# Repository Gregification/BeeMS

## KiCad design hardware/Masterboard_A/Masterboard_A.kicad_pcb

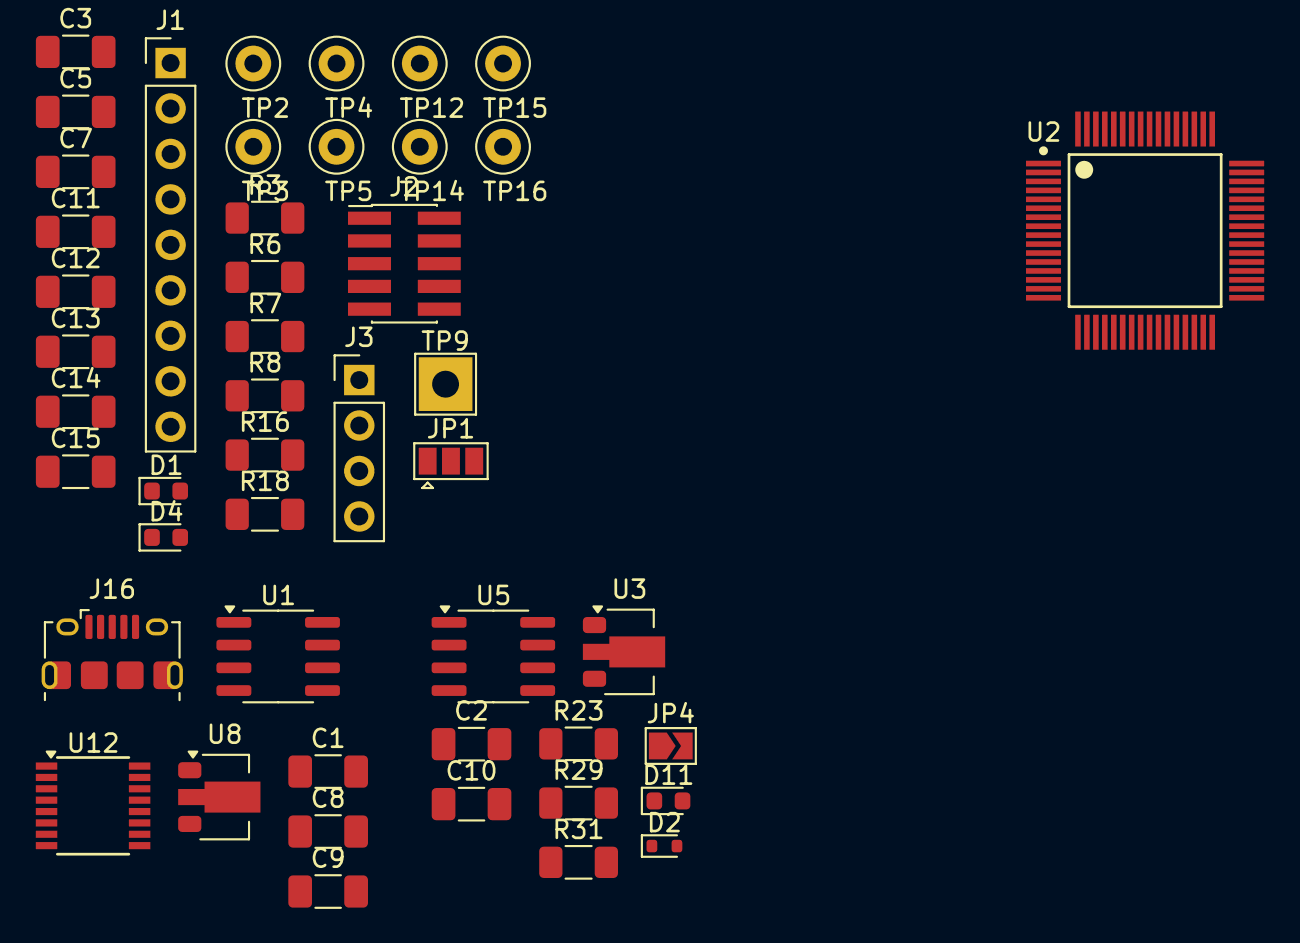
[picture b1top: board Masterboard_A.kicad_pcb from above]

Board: 2 copper layers, 47 parts (0 on the bottom side), 33 nets, no tracks yet.

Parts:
C1, C2, C8, C10, C14: 10u; C_1206_3216Metric_Pad1.33x1.80mm_HandSolder
C3, C15: 100n; C_1206_3216Metric_Pad1.33x1.80mm_HandSolder
C5, C7, C9, C11, C12, C13: 220n; C_1206_3216Metric_Pad1.33x1.80mm_HandSolder
D1, D4, D11: LED; LED_0603_1608Metric
D2: 1N4148WT; D_SOD-523
J1: Conn_01x09_Socket; PinHeader_1x09_P2.54mm_Vertical
J2: Conn_02x05_Odd_Even; PinHeader_2x05_P1.27mm_Vertical_SMD
J3: Conn_01x04_Pin; PinHeader_1x04_P2.54mm_Vertical
J16: USB_B_Micro; USB_Micro-B_Amphenol_10118194-0001LF_Horizontal
JP1: SolderJumper_3_Open; SolderJumper-3_P1.3mm_Open_Pad1.0x1.5mm
JP4: SolderJumper_2_Open; SolderJumper-2_P1.3mm_Open_TrianglePad1.0x1.5mm
R3, R6, R31: 750; R_1206_3216Metric_Pad1.30x1.75mm_HandSolder
R7, R23: 49.9k; R_1206_3216Metric_Pad1.30x1.75mm_HandSolder
R8: 100k; R_1206_3216Metric_Pad1.30x1.75mm_HandSolder
R16, R18, R29: 4.99k; R_1206_3216Metric_Pad1.30x1.75mm_HandSolder
TP2, TP3, TP4, TP5, TP12, TP14, TP15, TP16: TestPoint; TestPoint_Loop_D2.50mm_Drill1.0mm_LowProfile
TP9: TestPoint; TestPoint_THTPad_3.0x3.0mm_Drill1.5mm
U1, U5: ISO7721D; SOIC-8_3.9x4.9mm_P1.27mm
U2: MCU-MSM0G3507SPM; MSPM0G3507-64-IPC_A
U3, U8: L78L05_SOT89; SOT-89-3
U12: FT230XS; SSOP-16_3.9x4.9mm_P0.635mm

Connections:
/GLV CAN TRX/5v: JP4.2 (B), U5.1 (VCC1)
/GLV CAN TRX/-GLV: C2.2, C10.2, D11.1 (K), J3.3, R23.1, R29.2, U3.2 (GND), U5.4 (GND1)
/GLV CAN TRX/CAN_VDD: D2.2 (A), J3.4
/XDS_3v_supply: J1.3, J2.1, JP1.1 (A), TP5.1
GND: C3.2, C5.2, C7.2, C11.2, C12.2, C13.2, C14.2, C15.2, D1.1 (K), D4.1 (K), J1.1, J2.3, J2.5, J2.7, J2.9, R8.1, TP9.1, TP14.1, TP15.1, TP16.1, U1.5 (GND2), U2.41 (VSS), U5.5 (GND2)
unnamed: D1.2 (A), R6.1
unnamed: C10.1, D2.1 (K), U3.3 (IN)
unnamed: D4.2 (A), R3.2
unnamed: D11.2 (A), R31.2
unnamed: J16.3 (D+), U12.8 (USBDP)
unnamed: J16.2 (D-), U12.9 (USBDM)
unnamed: C1.2, C8.2, C9.2, J16.5 (GND), U1.4 (GND1), U8.2 (GND), U12.5 (GND), U12.13 (GND)
unnamed: C1.1, J16.1 (VBUS), U8.3 (IN)
unnamed: C2.1, JP4.1 (A), R31.1, U3.1 (OUT)
unnamed: U1.3 (INB), U12.1 (TXD)
unnamed: U1.2 (OUTA), U12.4 (RXD)
unnamed: C8.1, C9.1, U1.1 (VCC1), U8.1 (OUT), U12.3 (VCCIO), U12.12 (VCC)
unnamed: R8.2, U2.42 (PA2_ROSC)
unnamed: TP2.1, U2.64 (PB12)
unnamed: C5.1, C11.1, TP3.1, U2.32 (VCORE)
unnamed: R29.1, U5.2 (OUTA)
PA10_UART0-TX_XDS: J1.5, U1.7 (INA), U2.56 (PA10)
PA11_UART0-RX_XDS: J1.4, U1.6 (OUTB), U2.57 (PA11)
PA12_CAN_TX: U2.5 (PA12_CAN_TX), U5.7 (INA)
PA13_CAN_RX: U2.6 (PA13_CAN_RX), U5.6 (OUTB)
PA14: R3.1, U2.7 (PA14)
PA15_I2C1_SCL: R16.1, U2.8 (PA15_A1_0)
PA16_I2C1_SDA: R18.2, U2.9 (PA16_A1_1)
PA19_SWDIO: J1.7, J2.2, U2.12 (PA19_SWDIO)
PA20_SWCLK: J1.8, J2.4, U2.13 (PA20_SWCLK)
RST_N: C3.1, J1.6, J2.10, R7.2, U2.38 (RST_N)
VDD: C7.1, C12.1, C13.1, C14.1, C15.1, JP1.2 (C), R6.2, R7.1, R16.2, R18.1, TP4.1, U1.8 (VCC2), U2.40 (VDD), U5.8 (VCC2)
onboard 3.3v src: JP1.3 (B), TP12.1

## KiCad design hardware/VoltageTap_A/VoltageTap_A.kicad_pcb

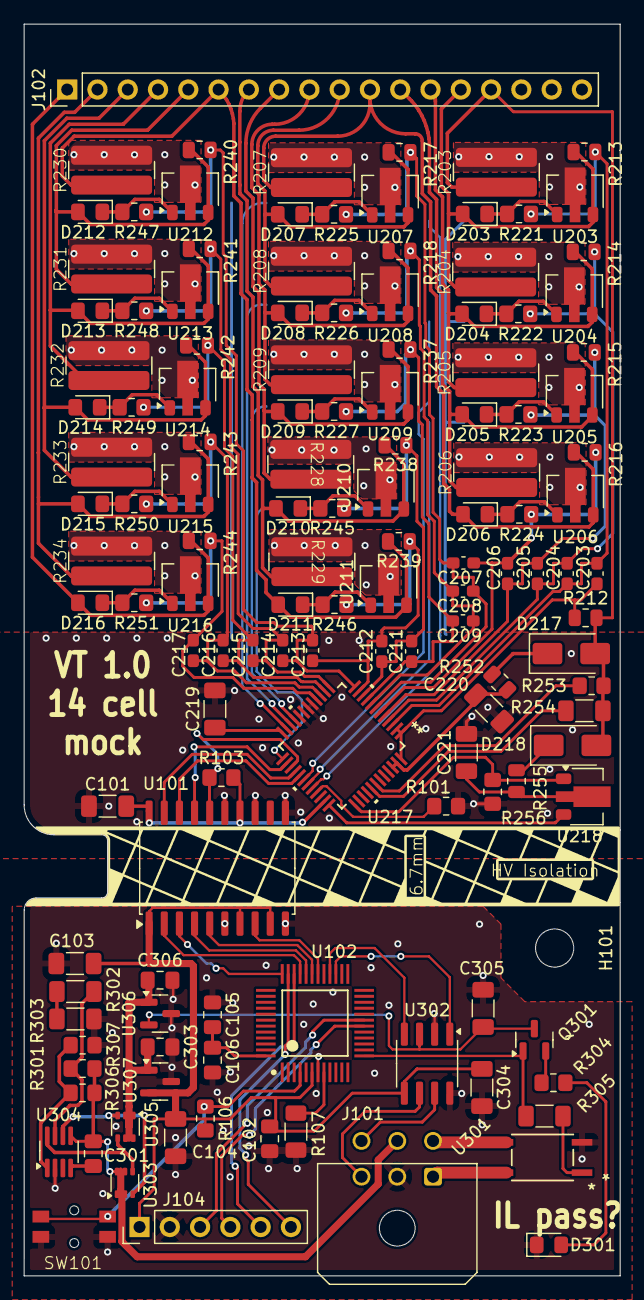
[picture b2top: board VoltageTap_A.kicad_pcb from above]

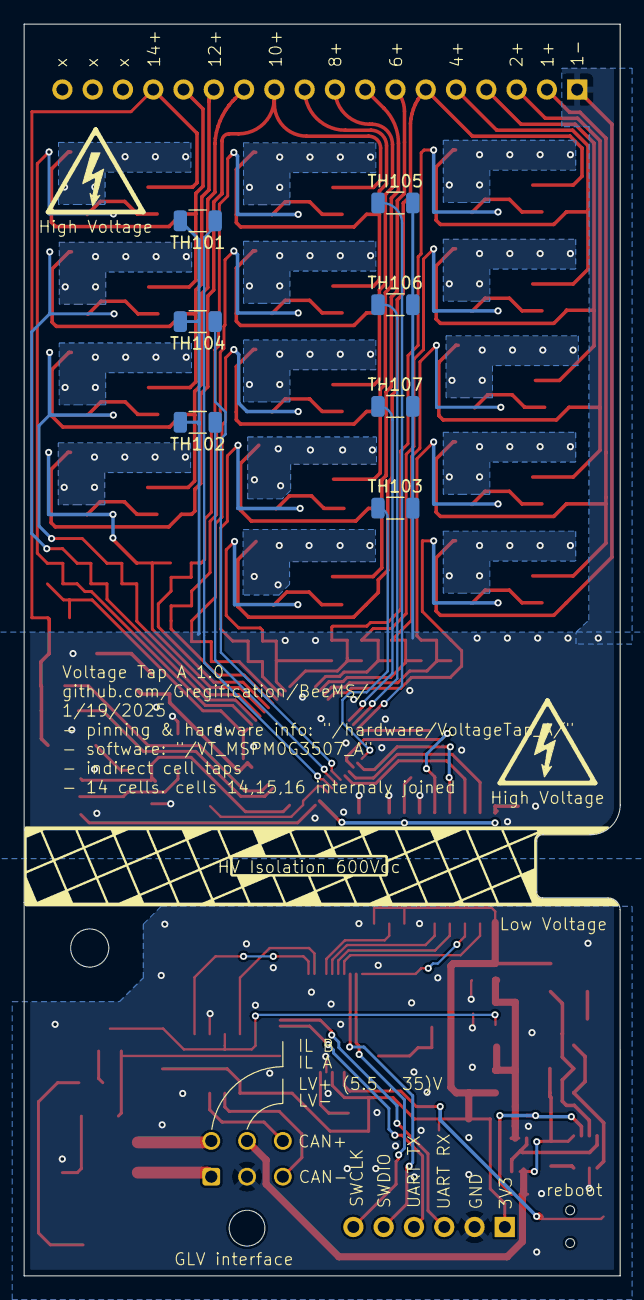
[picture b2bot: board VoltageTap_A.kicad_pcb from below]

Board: 2 copper layers, 50.0 x 105.0 mm, 142 parts (7 on the bottom side), 113 nets.

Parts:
C101, C103, C220, C221: 1u; C_1206_3216Metric_Pad1.33x1.80mm_HandSolder
C102, C105, C106, C301, C303, C306: 220n; C_0805_2012Metric_Pad1.18x1.45mm_HandSolder
C104, C219, C304, C305: 10u; C_1206_3216Metric_Pad1.33x1.80mm_HandSolder
C203, C204, C205, C206, C207, C208, C209, C211, C212, C213, C214, C215, C216, C217: 100n; C_0603_1608Metric_Pad1.08x0.95mm_HandSolder
D203, D204, D205, D206, D207, D208, D209, D210, D211, D212, D213, D214, D215, D216: TS4148; D_0805_2012Metric_Pad1.15x1.40mm_HandSolder
D217, D218: ES1D; D_SMA
D301: green; LED_0805_2012Metric_Pad1.15x1.40mm_HandSolder
H101: MountingHole; MountingHole_3.2mm_M3
J101: HRLV; Molex_Micro-Fit_3.0_43045-0600_2x03_P3.00mm_Horizontal
J102: Conn_01x18_Pin; PinHeader_1x18_P2.54mm_Vertical
J104: Conn_01x06_Pin; PinHeader_1x06_P2.54mm_Vertical
Q301: MMBT5550L; SOT-23
R101: 88.7k; R_0805_2012Metric_Pad1.20x1.40mm_HandSolder
R103, R253, R256, R307: 10k; R_0805_2012Metric_Pad1.20x1.40mm_HandSolder
R106: 40.2k; R_0805_2012Metric_Pad1.20x1.40mm_HandSolder
R107: 100k; R_1206_3216Metric_Pad1.30x1.75mm_HandSolder
R203, R204, R205, R206, R207, R208, R209, R228, R229, R230, R231, R232, R233, R234: 36; imperial wide resistor R_ 3264
R212, R213, R214, R215, R216, R217, R218, R237, R238, R239, R240, R241, R242, R243, R244, R252, R255: 100; R_0805_2012Metric
R221, R222, R223, R224, R225, R226, R227, R245, R246, R247, R248, R249, R250, R251: 226; R_0805_2012Metric_Pad1.20x1.40mm_HandSolder
R254, R302: 4.99k; R_1206_3216Metric_Pad1.30x1.75mm_HandSolder
R301, R306: 97.6k; R_0805_2012Metric_Pad1.20x1.40mm_HandSolder
R303, R305: 750; R_1206_3216Metric_Pad1.30x1.75mm_HandSolder
R304: 2.4k; R_0805_2012Metric_Pad1.20x1.40mm_HandSolder
SW101: SW_Push; wurth elektronik 4.7x3.5mm side push button
TH101, TH102, TH103, TH104, TH105, TH106, TH107: Thermistor; R_1206_3216Metric
U101: ISOW7741; SOIC-20W_7.5x12.8mm_P1.27mm
U102: XM0G3507QPTRQ1; PT0048A-IPC_B
U203, U204, U205, U206, U207, U208, U209, U210, U211, U212, U213, U214, U215, U216: 2PD2150-QX; SOT-89-3
U217: PBQ76952PFBT; BQ76952_PFB48_TEX
U218: FCX495; SOT-89-3
U301: ISOM8600DFGR; SOIC4_DFG_TEX-M
U302: MCP2542FDxMF; SOIC-8_3.9x4.9mm_P1.27mm
U303, U305: Si1450DH; SOT-363_SC-70-6
U304: LM74502; SOT-23-8_Handsoldering
U306: AP7384-50SA; SOT-23
U307: AP7381-33SA-7; SOT-23

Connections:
+3V3: C102.1, C103.1, C104.1, C304.1, J104.1, R106.2, U101.1 (V_{IO}), U101.7 (EN_IO1), U101.9 (V_{DD}), U102.6 (VDD), U302.5 (VIO), U307.2 (VO)
+BATT: D217.2 (A), D218.2 (A), J102.15, R203.2, R212.2, R253.2, R254.1
-BATT: C101.1, C219.2, C220.2, C221.2, D216.2 (A), J102.1, R101.1, R244.2, R256.1, TH101.2, TH102.2, TH103.2, TH104.2, TH105.2, TH106.2, TH107.2, U101.11 (GND2), U101.13 (VSEL), U101.15 (GISOIN), U216.3 (E), U217.17 (VSS), U217.18 (SRP), U217.20 (SRN)
/BQ0_3.3v: C101.2, R103.2, U101.14 (EN_IO2), U101.20 (V_{ISOIN}), U217.35 (REG1)
/BQ76952 16C/1P: D215.2 (A), J102.2, R234.2, R243.2, U215.3 (E)
/BQ76952 16C/2P: D214.2 (A), J102.3, R233.2, R242.2, U214.3 (E)
/BQ76952 16C/3P: D213.2 (A), J102.4, R232.2, R241.2, U213.3 (E)
/BQ76952 16C/4P: D212.2 (A), J102.5, R231.2, R240.2, U212.3 (E)
/BQ76952 16C/5P: D211.2 (A), J102.6, R230.2, R239.2, U211.3 (E)
/BQ76952 16C/6P: D210.2 (A), J102.7, R229.2, R238.2, U210.3 (E)
/BQ76952 16C/7P: D209.2 (A), J102.8, R228.2, R237.2, U209.3 (E)
/BQ76952 16C/8P: D208.2 (A), J102.9, R209.2, R218.2, U208.3 (E)
/BQ76952 16C/9P: D207.2 (A), J102.10, R208.2, R217.2, U207.3 (E)
/BQ76952 16C/10P: D206.2 (A), J102.11, R207.2, R216.2, U206.3 (E)
/BQ76952 16C/11P: D205.2 (A), J102.12, R206.2, R215.2, U205.3 (E)
/BQ76952 16C/12P: D204.2 (A), J102.13, R205.2, R214.2, U204.3 (E)
/BQ76952 16C/13P: D203.2 (A), J102.14, R204.2, R213.2, U203.3 (E)
/BQ76952 16C/ALERT: TH103.1, U217.25 (ALERT)
/BQ76952 16C/BAT: C220.1, R252.1, U217.46 (CP1), U217.47 (BAT)
/BQ76952 16C/C1Jc: R234.1, U216.2 (C)
/BQ76952 16C/C2Jc: R233.1, U215.2 (C)
/BQ76952 16C/C3Jc: R232.1, U214.2 (C)
/BQ76952 16C/C4Jc: R231.1, U213.2 (C)
/BQ76952 16C/C5Jc: R230.1, U212.2 (C)
/BQ76952 16C/C6Jc: R229.1, U211.2 (C)
/BQ76952 16C/C7Jc: R228.1, U210.2 (C)
/BQ76952 16C/C8Jc: R209.1, U209.2 (C)
/BQ76952 16C/C9Jc: R208.1, U208.2 (C)
/BQ76952 16C/C10Jc: R207.1, U207.2 (C)
/BQ76952 16C/C11Jc: R206.1, U206.2 (C)
/BQ76952 16C/C12Jc: R205.1, U205.2 (C)
/BQ76952 16C/C13Jc: R204.1, U204.2 (C)
/BQ76952 16C/C14Jc: R203.1, U203.2 (C)
/BQ76952 16C/CFETOFF: U101.18 (OUTB), U217.29 (CFETOFF)
/BQ76952 16C/DCHG: TH102.1, U217.31 (DCHG)
/BQ76952 16C/DDSG: TH101.1, U217.32 (DDSG)
/BQ76952 16C/DFETOFF: TH104.1, U217.30 (DFETOFF)
/BQ76952 16C/HDQ: U101.19 (OUTA), U217.28 (HDQ)
/BQ76952 16C/RST_SHUT: R101.2, U217.33 (RST_SHUT)
/BQ76952 16C/SCL: U101.17 (OUTC), U217.26 (SCL)
/BQ76952 16C/SDA: R103.1, U101.16 (IND), U217.27 (SDA)
/BQ76952 16C/TS1: TH107.1, U217.21 (TS1)
/BQ76952 16C/TS2: TH106.1, U217.22 (TS2)
/BQ76952 16C/TS3: TH105.1, U217.23 (TS3)
/CAN+: J101.6, U302.7 (CANH)
/CAN-: J101.3, U302.6 (CANL)
/GLV+: C301.1, J101.5, R301.2, R306.2, U303.1 (D), U303.2 (D), U303.5 (D), U303.6 (D), U304.5 (VS)
/HRLV interface/+5V: C305.1, Q301.3 (C), U302.3 (VDD), U306.2 (VO)
/HRLV interface/CAN_RX: U102.28 (PA13), U302.4 (RXD)
/HRLV interface/CAN_TX: U102.27 (PA12_FCC_IN), U302.1 (TXD)
/HRLV interface/IL enable: Q301.1 (B), R305.2, U102.13 (PA7_CLK_OUT)
/HRLV interface/LV+: C303.1, C306.1, U305.1 (D), U305.2 (D), U305.5 (D), U305.6 (D), U306.1 (VI), U307.1 (VI)
/HRLV interface/passing: U303.4 (S), U304.8 (SRC), U305.4 (S)
/IL+: J101.1, U301.4
/IL-: J101.4, U301.3
GND: C102.2, C103.2, C104.2, C105.2, C106.2, C303.2, C304.2, C305.2, C306.2, D301.1 (K), J101.2, J104.2, R107.1, R303.1, R307.1, SW101.2, U101.6 (GNDIO), U101.10 (GND1), U102.7 (VSS), U301.2, U302.2 (VSS), U302.8 (STBY), U304.2 (GND), U306.3 (GND), U307.3 (GND)
unnamed: C221.1, R255.1, U218.2
unnamed: D203.1 (K), R221.2, U203.1 (B)
unnamed: D204.1 (K), R222.2, U204.1 (B)
unnamed: D205.1 (K), R223.2, U205.1 (B)
unnamed: D206.1 (K), R224.2, U206.1 (B)
unnamed: D207.1 (K), R225.2, U207.1 (B)
unnamed: D208.1 (K), R226.2, U208.1 (B)
unnamed: D209.1 (K), R227.2, U209.1 (B)
unnamed: D210.1 (K), R245.2, U210.1 (B)
unnamed: D211.1 (K), R246.2, U211.1 (B)
unnamed: D212.1 (K), R247.2, U212.1 (B)
unnamed: D213.1 (K), R248.2, U213.1 (B)
unnamed: D214.1 (K), R249.2, U214.1 (B)
unnamed: D215.1 (K), R250.2, U215.1 (B)
unnamed: D216.1 (K), R251.2, U216.1 (B)
unnamed: D217.1 (K), R252.2
unnamed: D218.1 (K), R255.2
unnamed: D301.2 (A), R304.1
unnamed: Q301.2 (E), R304.2
unnamed: R302.1, R303.2
unnamed: R305.1, U301.1
unnamed: R107.2, U102.8 (PA2_ROSC)
unnamed: C105.1, C106.1, U102.48 (VCORE)
unnamed: R256.2, U217.37 (BREG), U218.1
unnamed: R254.2, U217.41 (LD)
unnamed: R253.1, U217.42 (PACK)
unnamed: C219.1, U217.24 (REG18)
unnamed: U217.36 (REGIN), U218.3
unnamed: C217.2, R244.1, R251.1, U217.16 (VC0)
unnamed: C216.2, C217.1, R243.1, R250.1, U217.15 (VC1)
unnamed: C215.2, C216.1, R242.1, R249.1, U217.14 (VC2)
unnamed: C214.2, C215.1, R241.1, R248.1, U217.13 (VC3)
unnamed: C213.2, C214.1, R240.1, R247.1, U217.12 (VC4)
unnamed: C212.2, C213.1, R239.1, R246.1, U217.11 (VC5)
unnamed: C211.2, C212.1, R238.1, R245.1, U217.10 (VC6)
unnamed: C209.2, C211.1, R227.1, R237.1, U217.9 (VC7)
unnamed: C208.2, C209.1, R218.1, R226.1, U217.8 (VC8)
unnamed: C207.2, C208.1, R217.1, R225.1, U217.7 (VC9)
unnamed: C206.2, C207.1, R216.1, R224.1, U217.6 (VC10)
unnamed: C205.2, C206.1, R215.1, R223.1, U217.5 (VC11)
unnamed: C204.2, C205.1, R214.1, R222.1, U217.4 (VC12)
unnamed: C203.2, C204.1, R213.1, R221.1, U217.3 (VC13)
unnamed: C203.1, R212.1, U217.1 (VC15), U217.2 (VC14), U217.48 (VC16)
unnamed: U303.3 (G), U304.6 (GATE), U305.3 (G)
unnamed: R306.1, R307.2, U304.1 (EN/UVLO)
unnamed: R301.1, R302.2, U304.7 (OV)
unnamed: C301.2, U304.4 (VCAP)
PA10_UART0-TX_XDS: J104.4, U102.18 (PA10_CLK_OUT)
PA11_UART0-RX_XDS: J104.3, U102.19 (PA11)
PA16_SPI1_MISO: U101.5 (OUTD), U102.31 (PA16_A1_1_FCC_IN)
PA17_SPI1_SCK: U101.4 (INC), U102.32 (PA17_A1_2)
PA18_SPI1_MOSI: U101.2 (INA), U102.33 (PA18_A1_3)
PA19_SWDIO: J104.5, U102.34 (PA19_SWDIO)
PA20_SWCLK: J104.6, U102.35 (PA20_SWCLK)
PA20_SWCLK_EN/FLT: U101.8 (EN/FLT), U102.30 (PA15_A1_0)
PB17_BBQ_CS: U101.3 (INB), U102.36 (PB17_A1_4)
RST_N: R106.1, SW101.1, U102.4 (RST_N)

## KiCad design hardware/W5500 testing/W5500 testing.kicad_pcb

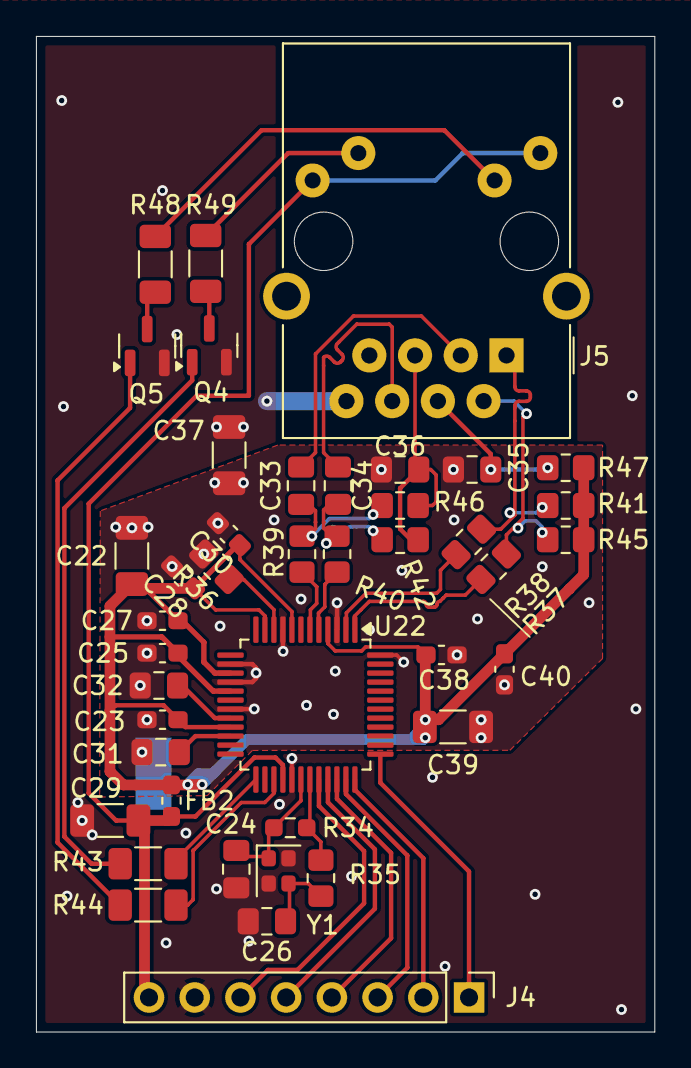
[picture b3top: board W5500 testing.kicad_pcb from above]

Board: 2 copper layers, 34.4 x 55.3 mm, 43 parts (1 on the bottom side), 36 nets.

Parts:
C22, C29, C39: 10u; C_1206_3216Metric_Pad1.33x1.80mm_HandSolder
C23, C25, C27, C28, C30, C38, C40: 100n; C_0603_1608Metric_Pad1.08x0.95mm_HandSolder
C24, C26: 18p; C_0805_2012Metric_Pad1.18x1.45mm_HandSolder
C31, C36: 10n; C_0805_2012Metric_Pad1.18x1.45mm_HandSolder
C32: 4.7u; C_0805_2012Metric_Pad1.18x1.45mm_HandSolder
C33, C34: 6.8n; C_0805_2012Metric_Pad1.18x1.45mm_HandSolder
C35: 22n; C_0805_2012Metric_Pad1.18x1.45mm_HandSolder
C37: 1n 2kV; C_1206_3216Metric_Pad1.33x1.80mm_HandSolder
FB2: L_0603_1608Metric_Pad1.05x0.95mm_HandSolder
J4: Conn_01x08_Pin; PinHeader_1x08_P2.54mm_Vertical
J5: RJ45_Amphenol_RJMG1BD3B8K1ANR
NT1: NetTie_2; NetTie-2_SMD_Pad2.0mm
Q4, Q5: MMBT5550L; SOT-23
R34: 1M; R_0603_1608Metric_Pad0.98x0.95mm_HandSolder
R35: 0; R_0805_2012Metric_Pad1.20x1.40mm_HandSolder
R36: 12.4k; R_0805_2012Metric_Pad1.20x1.40mm_HandSolder
R37, R38, R39, R40: 14.3; R_0805_2012Metric_Pad1.20x1.40mm_HandSolder
R41, R42, R45, R46: 49.9; R_0805_2012Metric_Pad1.20x1.40mm_HandSolder
R43, R44: 4.99k; R_1206_3216Metric_Pad1.30x1.75mm_HandSolder
R47: 10; R_0805_2012Metric_Pad1.20x1.40mm_HandSolder
R48, R49: 332; R_1206_3216Metric_Pad1.30x1.75mm_HandSolder
U22: W5500; LQFP-48_7x7mm_P0.5mm
Y1: Crystal_GND24; Crystal_SMD_2016-4Pin_2.0x1.6mm

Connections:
/3v3: C29.1, FB2.1, J4.8, J5.L1, J5.L4, U22.28 (VDD)
/GND: C24.2, C26.2, C29.2, C37.1, J4.7, J5.R8, NT1.2, Q4.2 (E), Q5.2 (E), U22.29 (GND), Y1.2, Y1.4
/W5500/+3.3VA: C22.1, C23.1, C25.1, C27.1, C28.1, C30.1, C38.1, C39.1, C40.1, FB2.2, R41.2, R45.2, R47.1, U22.4 (AVDD), U22.8 (AVDD), U22.11 (AVDD), U22.15 (AVDD), U22.17 (AVDD), U22.21 (AVDD)
/W5500/AGND: C22.2, C23.2, C25.2, C27.2, C28.2, C30.2, C31.2, C32.2, C35.2, C36.2, C37.2, C38.2, C39.2, C40.2, NT1.1, R36.2, U22.3 (AGND), U22.9 (AGND), U22.14 (AGND), U22.16 (AGND), U22.19 (AGND), U22.48 (AGND)
/W5500/CS_N: J4.6, U22.32 (~SCS)
/W5500/INT_N: J4.2, U22.36 (~INT)
/W5500/MISO: J4.4, U22.34 (MISO)
/W5500/MOSI: J4.3, U22.35 (MOSI)
/W5500/RD+: C33.2, J5.R3 (RD+)
/W5500/RD-: C34.2, J5.R6 (RD-)
/W5500/RST_N: J4.1, U22.37 (~RST)
/W5500/RX+: R39.2, U22.6 (RXP)
/W5500/RX-: R40.1, U22.5 (RXN)
/W5500/RX_1+: C33.1, R39.1, R46.2
/W5500/RX_1-: C34.1, R40.2, R42.2
/W5500/SCLK: J4.5, U22.33 (SCLK)
/W5500/TD+: J5.R1 (TD+), R37.1, R41.1
/W5500/TD-: J5.R2 (TD-), R38.2, R45.1
/W5500/TX+: R37.2, U22.2 (TXP)
/W5500/TX-: R38.1, U22.1 (TXN)
unnamed: C26.1, R35.2, Y1.3
unnamed: J5.L2, R48.2
unnamed: J5.L3, R49.1
unnamed: C36.1, J5.R5 (RCT), R42.1, R46.1
unnamed: C35.1, J5.R4 (TCT), R47.2
unnamed: Q4.1 (B), R43.2
unnamed: Q4.3 (C), R48.1
unnamed: Q5.1 (B), R44.1
unnamed: Q5.3 (C), R49.2
unnamed: C31.1, U22.22 (1V2O)
unnamed: R44.2, U22.27 (ACTLED)
unnamed: R36.1, U22.10 (EXRES1)
unnamed: R43.1, U22.25 (LINKLED)
unnamed: C32.1, U22.20 (TOCAP)
unnamed: C24.1, R34.1, U22.30 (XI/CLKIN), Y1.1
unnamed: R34.2, R35.1, U22.31 (XO)

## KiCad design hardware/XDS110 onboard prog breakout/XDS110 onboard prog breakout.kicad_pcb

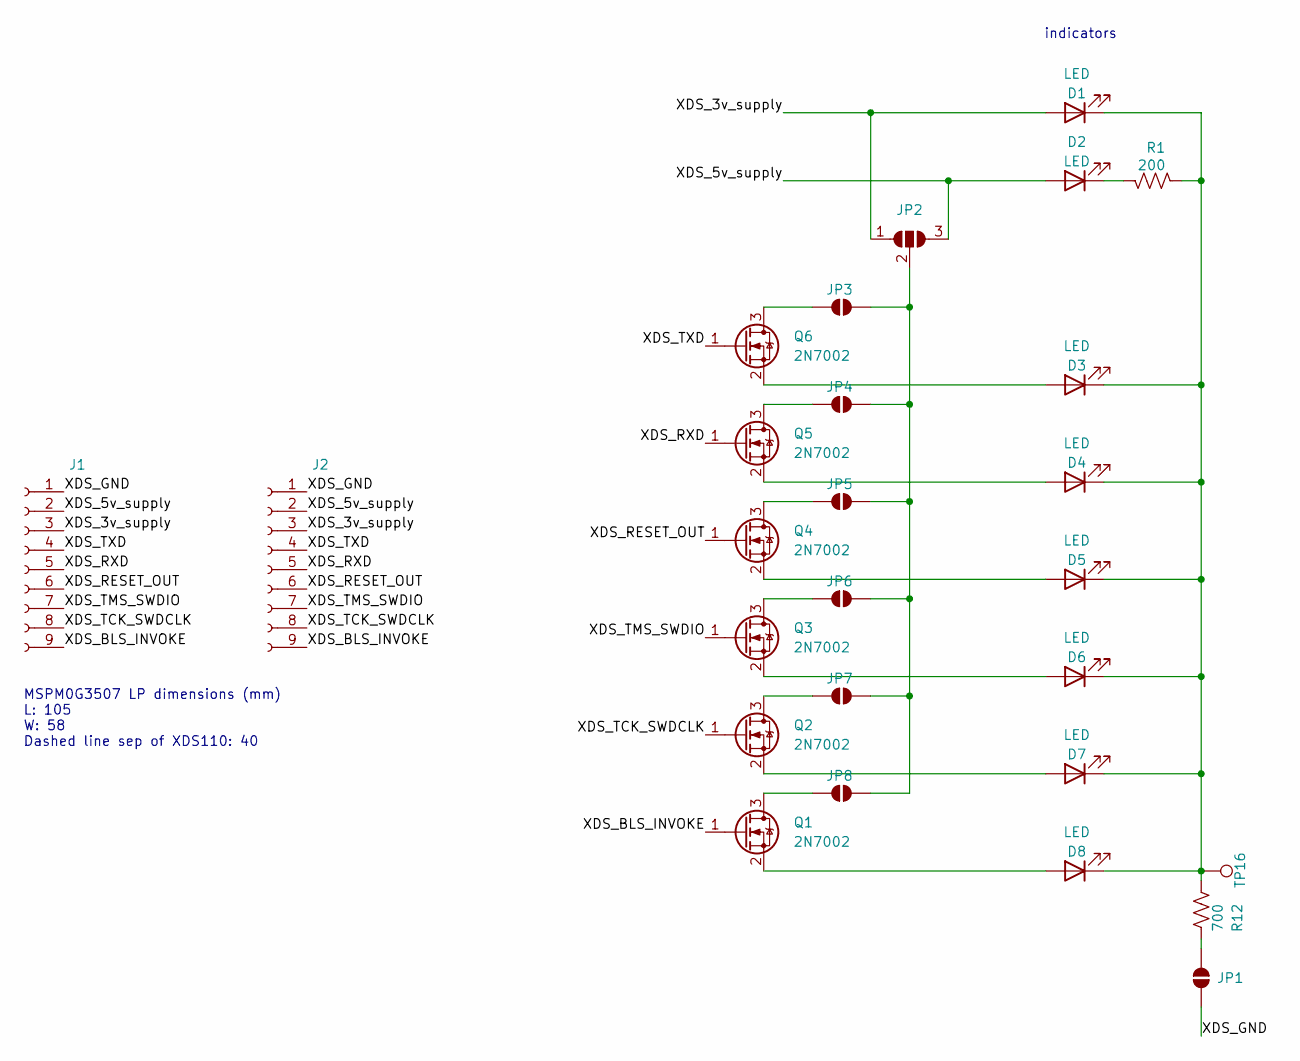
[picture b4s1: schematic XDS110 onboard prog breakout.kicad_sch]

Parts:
D1, D2, D3, D4, D5, D6, D7, D8: LED; LED_0201_0603Metric_Pad0.64x0.40mm_HandSolder
J1, J2: Conn_01x09_Socket; PinHeader_1x09_P2.54mm_Vertical
JP1, JP3, JP4, JP5, JP6, JP7, JP8: SolderJumper_2_Open; SolderJumper-2_P1.3mm_Open_RoundedPad1.0x1.5mm
JP2: SolderJumper_3_Open; SolderJumper-3_P1.3mm_Open_Pad1.0x1.5mm
Q1, Q2, Q3, Q4, Q5, Q6: 2N7002; SOT-23
R1: 200; R_1206_3216Metric_Pad1.30x1.75mm_HandSolder
R12: 700; R_1206_3216Metric_Pad1.30x1.75mm_HandSolder
TP16: TestPoint; TestPoint_Loop_D2.50mm_Drill1.0mm_LowProfile

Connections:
/XDS_3v_supply: D1.2 (A), J1.3, J2.3, JP2.1 (A)
/XDS_5v_supply: D2.2 (A), J1.2, J2.2, JP2.3 (B)
/XDS_BLS_INVOKE: J1.9, J2.9, Q1.1 (G)
/XDS_GND: J1.1, J2.1, JP1.1 (A)
/XDS_RESET_OUT: J1.6, J2.6, Q4.1 (G)
/XDS_RXD: J1.5, J2.5, Q5.1 (G)
/XDS_TCK_SWDCLK: J1.8, J2.8, Q2.1 (G)
/XDS_TMS_SWDIO: J1.7, J2.7, Q3.1 (G)
/XDS_TXD: J1.4, J2.4, Q6.1 (G)
unnamed: D1.1 (K), D3.1 (K), D4.1 (K), D5.1 (K), D6.1 (K), D7.1 (K), D8.1 (K), R1.2, R12.2, TP16.1
unnamed: D2.1 (K), R1.1
unnamed: D3.2 (A), Q6.2 (S)
unnamed: D4.2 (A), Q5.2 (S)
unnamed: D5.2 (A), Q4.2 (S)
unnamed: D6.2 (A), Q3.2 (S)
unnamed: D7.2 (A), Q2.2 (S)
unnamed: D8.2 (A), Q1.2 (S)
unnamed: JP1.2 (B), R12.1
unnamed: JP2.2 (C), JP3.2 (B), JP4.2 (B), JP5.2 (B), JP6.2 (B), JP7.2 (B), JP8.2 (B)
unnamed: JP3.1 (A), Q6.3 (D)
unnamed: JP4.1 (A), Q5.3 (D)
unnamed: JP5.1 (A), Q4.3 (D)
unnamed: JP6.1 (A), Q3.3 (D)
unnamed: JP7.1 (A), Q2.3 (D)
unnamed: JP8.1 (A), Q1.3 (D)

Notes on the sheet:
indicators
MSPM0G3507 LP dimensions (mm) L: 105 W: 58 Dashed line sep of XDS110: 40

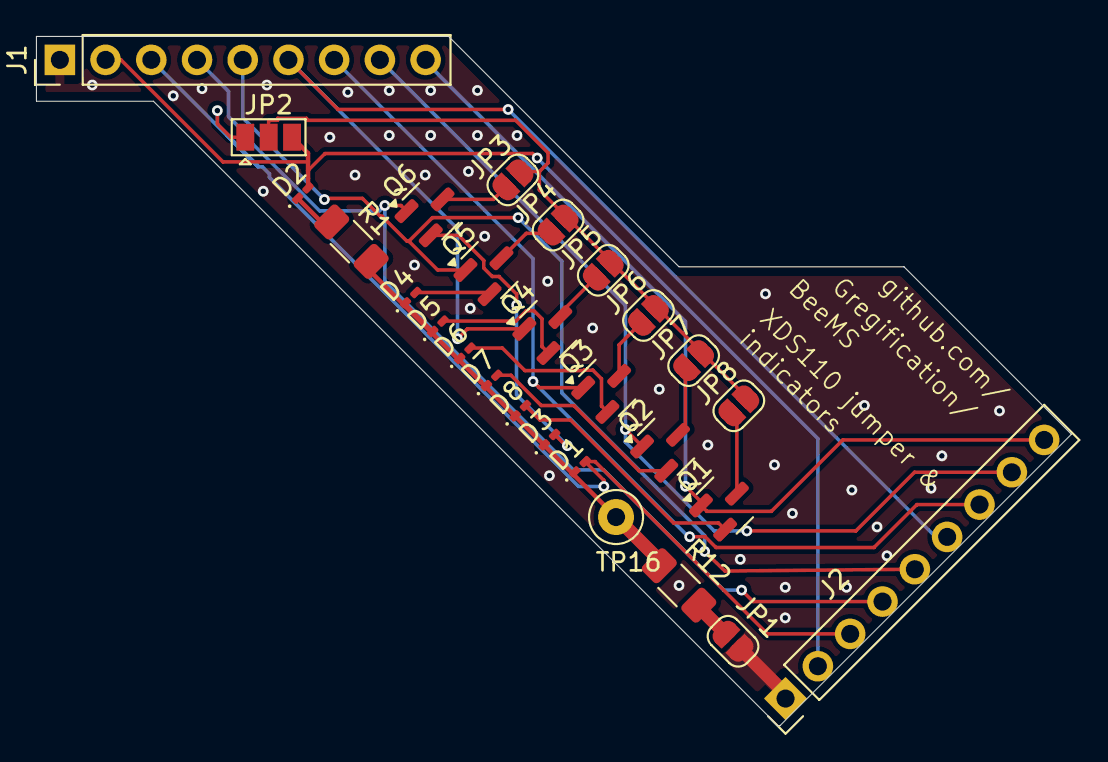
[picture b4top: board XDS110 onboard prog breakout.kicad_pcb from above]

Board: 2 copper layers, 57.5 x 38.3 mm, 27 parts (0 on the bottom side), 25 nets.

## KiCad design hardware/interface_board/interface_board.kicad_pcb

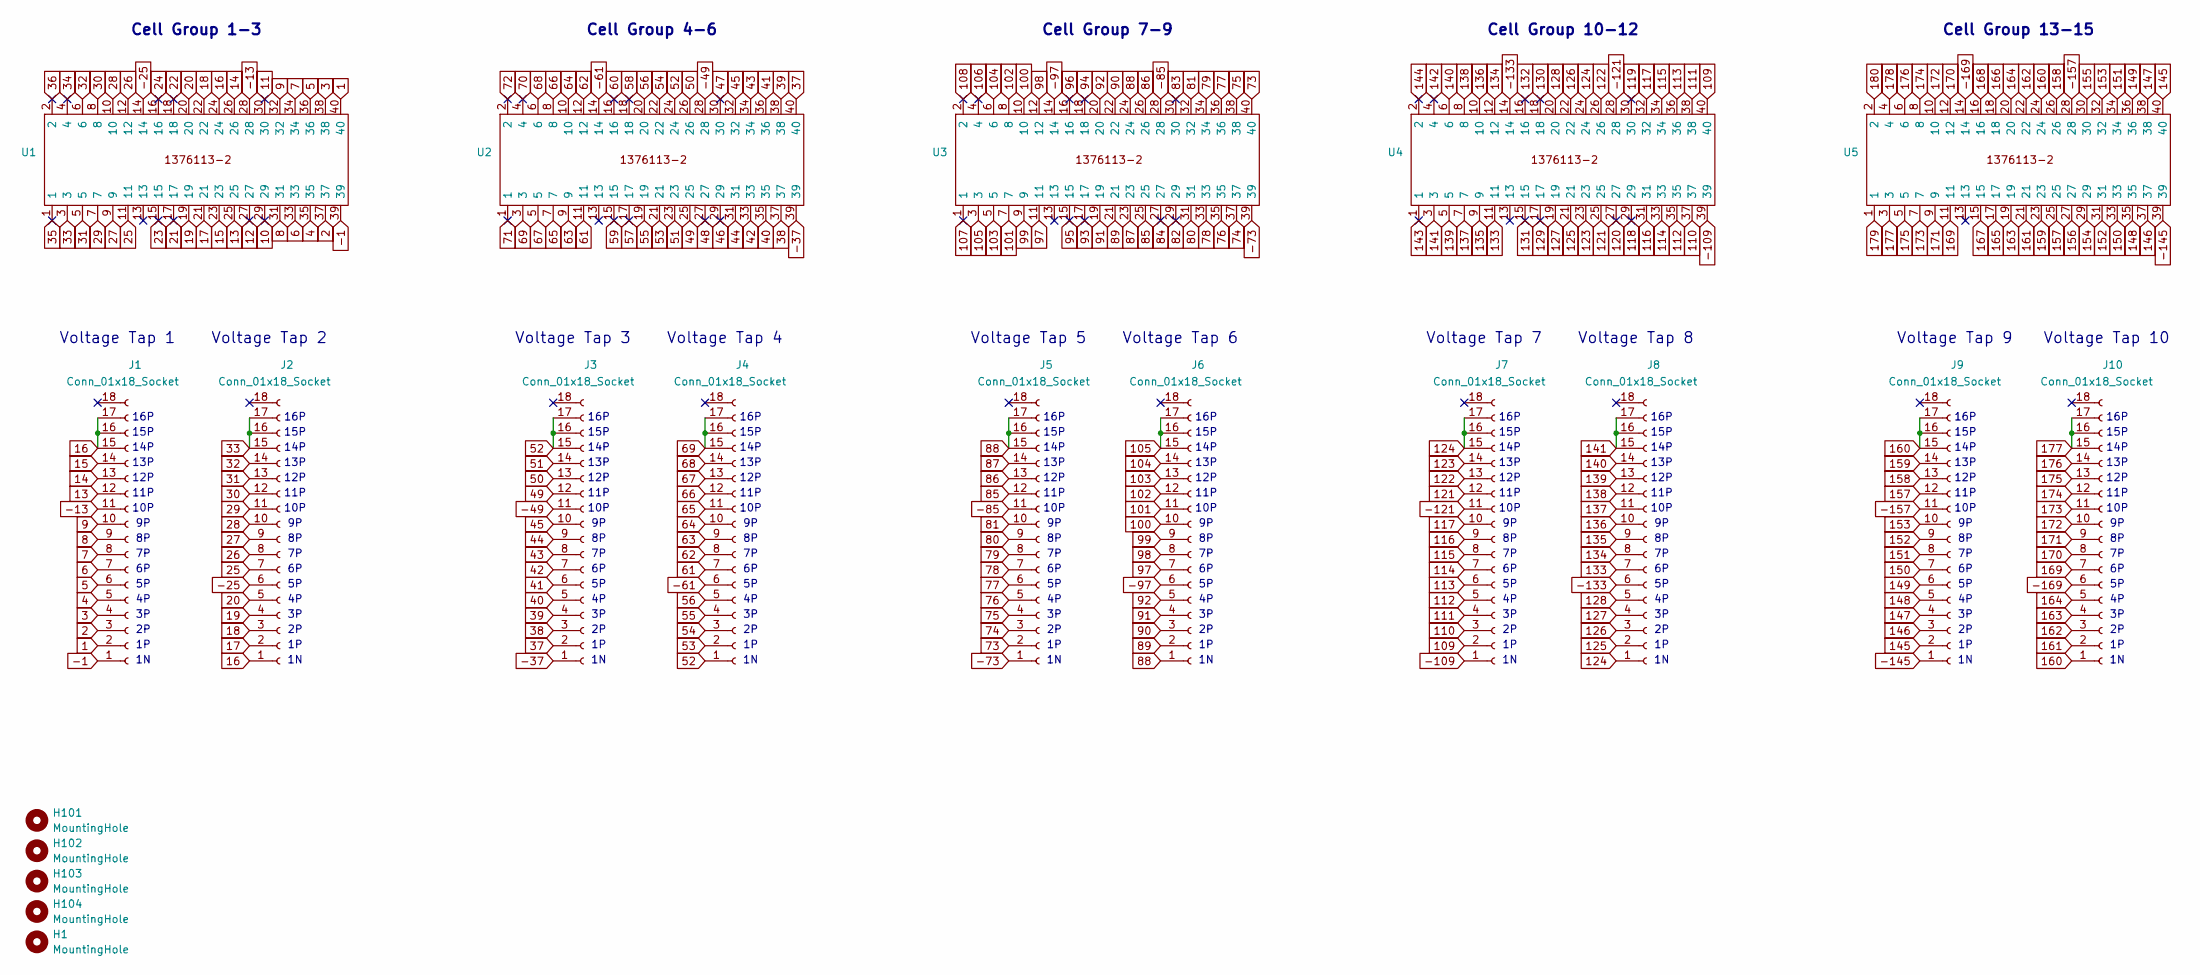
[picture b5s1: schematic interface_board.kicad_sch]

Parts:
H1, H101, H102, H103, H104: MountingHole; MountingHole_3.2mm_M3
J1, J2, J3, J4, J5, J6, J7, J8, J9, J10: Conn_01x18_Socket; PinSocket_1x18_P2.54mm_Vertical
U1, U2, U3, U4, U5: 13761132; Manufacturer_Part_Number 1376113-2; Mouser Part Number 571-1376113-2

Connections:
1: J1.2, U1.40
2: J1.3, U1.37
3: J1.4, U1.38
4: J1.5, U1.35
5: J1.6, U1.36
6: J1.7, U1.33
7: J1.8, U1.34
8: J1.9, U1.31
9: J1.10, U1.32
10: U1.29
11: U1.30
12: U1.27
13: J1.12, U1.25
14: J1.13, U1.26
15: J1.14, U1.23
16: J1.15, J1.16, J1.17, J2.1, U1.24
17: J2.2, U1.21
18: J2.3, U1.22
19: J2.4, U1.19
20: J2.5, U1.20
21: U1.17
22: U1.18
23: U1.15
24: U1.16
25: J2.7, U1.11
26: J2.8, U1.12
27: J2.9, U1.9
28: J2.10, U1.10
29: J2.11, U1.7
30: J2.12, U1.8
31: J2.13, U1.5
32: J2.14, U1.6
33: J2.15, J2.16, J2.17, U1.3
34: U1.4
35: U1.1
36: U1.2
37: J3.2, U2.40
38: J3.3, U2.37
39: J3.4, U2.38
40: J3.5, U2.35
41: J3.6, U2.36
42: J3.7, U2.33
43: J3.8, U2.34
44: J3.9, U2.31
45: J3.10, U2.32
46: U2.29
47: U2.30
48: U2.27
49: J3.12, U2.25
50: J3.13, U2.26
51: J3.14, U2.23
52: J3.15, J3.16, J3.17, J4.1, U2.24
53: J4.2, U2.21
54: J4.3, U2.22
55: J4.4, U2.19
56: J4.5, U2.20
57: U2.17
58: U2.18
59: U2.15
60: U2.16
61: J4.7, U2.11
62: J4.8, U2.12
63: J4.9, U2.9
64: J4.10, U2.10
65: J4.11, U2.7
66: J4.12, U2.8
67: J4.13, U2.5
68: J4.14, U2.6
69: J4.15, J4.16, J4.17, U2.3
70: U2.4
71: U2.1
72: U2.2
73: J5.2, U3.40
74: J5.3, U3.37
75: J5.4, U3.38
76: J5.5, U3.35
77: J5.6, U3.36
78: J5.7, U3.33
79: J5.8, U3.34
80: J5.9, U3.31
81: J5.10, U3.32
82: U3.29
83: U3.30
84: U3.27
85: J5.12, U3.25
86: J5.13, U3.26
87: J5.14, U3.23
88: J5.15, J5.16, J5.17, J6.1, U3.24
89: J6.2, U3.21
90: J6.3, U3.22
91: J6.4, U3.19
92: J6.5, U3.20
93: U3.17
94: U3.18
95: U3.15
96: U3.16
97: J6.7, U3.11
98: J6.8, U3.12
99: J6.9, U3.9
100: J6.10, U3.10
101: J6.11, U3.7
102: J6.12, U3.8
103: J6.13, U3.5
104: J6.14, U3.6
105: J6.15, J6.16, J6.17, U3.3
106: U3.4
107: U3.1
108: U3.2
109: J7.2, U4.40
110: J7.3, U4.37
111: J7.4, U4.38
112: J7.5, U4.35
113: J7.6, U4.36
114: J7.7, U4.33
115: J7.8, U4.34
116: J7.9, U4.31
117: J7.10, U4.32
118: U4.29
119: U4.30
120: U4.27
121: J7.12, U4.25
122: J7.13, U4.26
123: J7.14, U4.23
124: J7.15, J7.16, J7.17, J8.1, U4.24
125: J8.2, U4.21
126: J8.3, U4.22
127: J8.4, U4.19
128: J8.5, U4.20
129: U4.17
130: U4.18
131: U4.15
132: U4.16
133: J8.7, U4.11
134: J8.8, U4.12
135: J8.9, U4.9
136: J8.10, U4.10
137: J8.11, U4.7
138: J8.12, U4.8
139: J8.13, U4.5
140: J8.14, U4.6
141: J8.15, J8.16, J8.17, U4.3
142: U4.4
143: U4.1
144: U4.2
145: J9.2, U5.40
146: J9.3, U5.37
147: J9.4, U5.38
148: J9.5, U5.35
149: J9.6, U5.36
150: J9.7, U5.33
151: J9.8, U5.34
152: J9.9, U5.31
153: J9.10, U5.32
154: U5.29
155: U5.30
156: U5.27
157: J9.12, U5.25
158: J9.13, U5.26
159: J9.14, U5.23
160: J9.15, J9.16, J9.17, J10.1, U5.24
161: J10.2, U5.21
162: J10.3, U5.22
163: J10.4, U5.19
164: J10.5, U5.20
165: U5.17
166: U5.18
167: U5.15
168: U5.16
169: J10.7, U5.11
170: J10.8, U5.12
171: J10.9, U5.9
172: J10.10, U5.10
173: J10.11, U5.7
174: J10.12, U5.8
175: J10.13, U5.5
176: J10.14, U5.6
177: J10.15, J10.16, J10.17, U5.3
178: U5.4
179: U5.1
180: U5.2
-1: J1.1, U1.39
-13: J1.11, U1.28
-25: J2.6, U1.14
-37: J3.1, U2.39
-49: J3.11, U2.28
-61: J4.6, U2.14
-73: J5.1, U3.39
-85: J5.11, U3.28
-97: J6.6, U3.14
-109: J7.1, U4.39
-121: J7.11, U4.28
-133: J8.6, U4.14
-145: J9.1, U5.39
-157: J9.11, U5.28
-169: J10.6, U5.14

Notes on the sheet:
Voltage Tap 10
Voltage Tap 9
10P
12P
15P
Voltage Tap 7
13P
Cell Group 7-9
Cell Group 10-12
16P
11P
14P
Voltage Tap 4
Cell Group 1-3
Voltage Tap 5
Cell Group 4-6
Voltage Tap 1
Voltage Tap 6
Cell Group 13-15
Voltage Tap 2
Voltage Tap 8
Voltage Tap 3

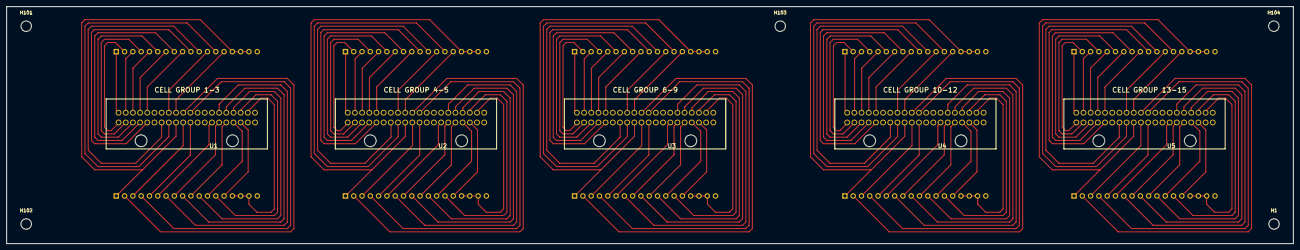
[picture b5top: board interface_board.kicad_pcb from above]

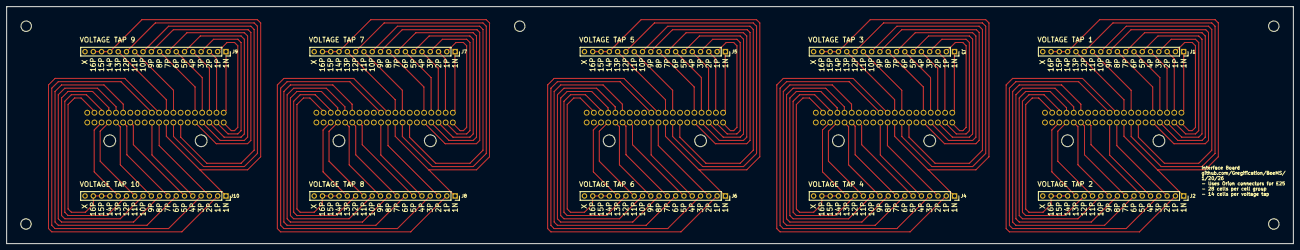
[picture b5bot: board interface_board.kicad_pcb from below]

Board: 2 copper layers, 394.2 x 72.6 mm, 20 parts (10 on the bottom side), 145 nets.
